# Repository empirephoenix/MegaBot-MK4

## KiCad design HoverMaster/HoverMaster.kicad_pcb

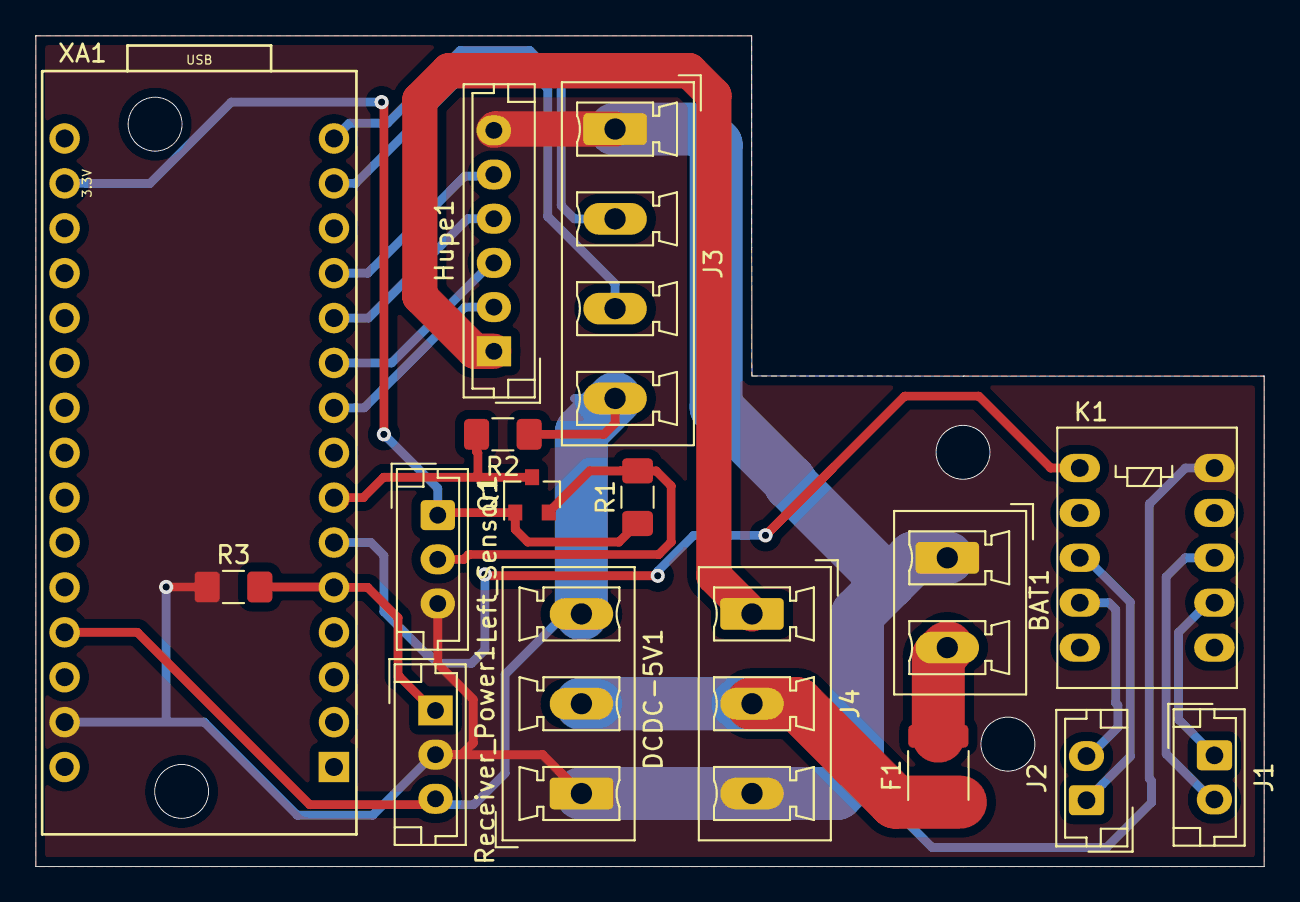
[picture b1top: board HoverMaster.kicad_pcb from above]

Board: 2 copper layers, 69.5 x 47.0 mm, 16 parts (0 on the bottom side), 20 nets.

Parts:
BAT1: Conn_01x02_Male; PhoenixContact_MCV_1,5_2-G-5.08_1x02_P5.08mm_Vertical
DCDC-5V1: Conn_01x03_Male; PhoenixContact_MCV_1,5_3-G-5.08_1x03_P5.08mm_Vertical
F1: Fuse; Fuse_1812_4532Metric_Pad1.30x3.40mm_HandSolder
Hupe1: Conn_01x06_Male; JST_EH_B06B-EH-A_1x06_P2.50mm_Vertical
J1, J2: Conn_01x02_Male; JST_EH_B2B-EH-A_1x02_P2.50mm_Vertical
J3: LED; PhoenixContact_MCV_1,5_4-G-5.08_1x04_P5.08mm_Vertical
J4: Conn_01x03_Female; PhoenixContact_MCV_1,5_3-G-5.08_1x03_P5.08mm_Vertical
K1: FRT5; Relay_DPDT_FRT5
Left_Sensor1: Conn_01x03; JST_EH_B3B-EH-A_1x03_P2.50mm_Vertical
Q1: BSS138; SOT-23
R1, R2: 10K; R_1206_3216Metric_Pad1.42x1.75mm_HandSolder
R3: 10kOhm; R_1206_3216Metric_Pad1.42x1.75mm_HandSolder
Receiver_Power1: Conn_01x04; JST_EH_B03B-EH-A_1x03_P2.50mm_Vertical
XA1: Arduino_Nano_Socket

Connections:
3.3V: Left_Sensor1.1, Q1.1, R1.1, XA1.3V3
5V: DCDC-5V1.3, J3.4, R2.1, Receiver_Power1.3, XA1.5V
12V: Hupe1.1, J4.1
BAT+: BAT1.2, F1.2
BAT_Fuse+: DCDC-5V1.2, F1.1, J4.2
GND: BAT1.1, DCDC-5V1.1, Hupe1.6, J3.1, J4.3, K1.10, Left_Sensor1.3, R3.1, Receiver_Power1.2, XA1.GND2
HOVER_POWER_RELAY: K1.1, XA1.D3
Hupe_1: Hupe1.2, XA1.D6
Hupe_2: Hupe1.3, XA1.D7
Hupe_3: Hupe1.4, XA1.D8
Hupe_4: Hupe1.5, XA1.D9
LED1: J3.2, XA1.D12
LED2: J3.3, XA1.D11
unnamed: J1.1, K1.7
unnamed: J1.2, K1.8
unnamed: J2.1, K1.3
unnamed: J2.2, K1.4
unnamed: Left_Sensor1.2, Q1.2, R1.2
PPM_IN: R3.2, Receiver_Power1.1, XA1.D2
PPM_OUT: Q1.3, R2.2, XA1.D4

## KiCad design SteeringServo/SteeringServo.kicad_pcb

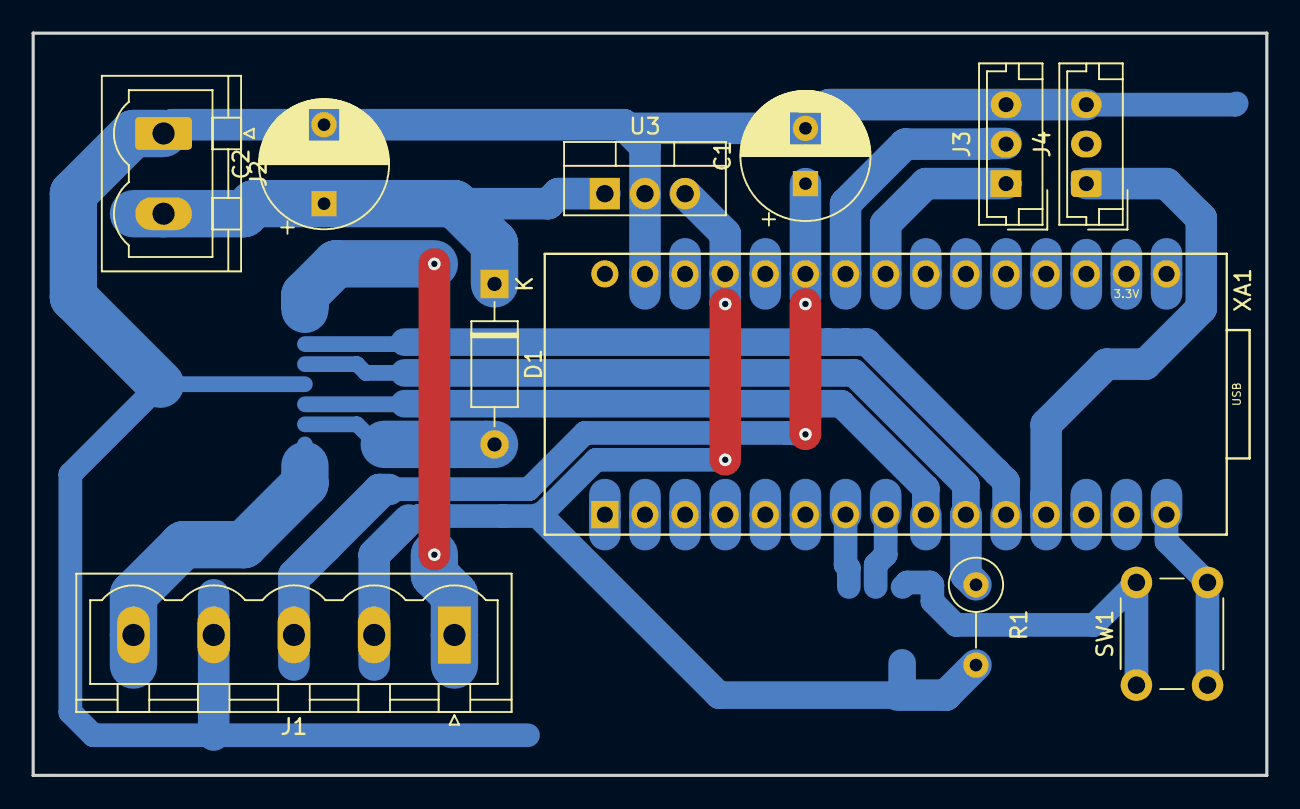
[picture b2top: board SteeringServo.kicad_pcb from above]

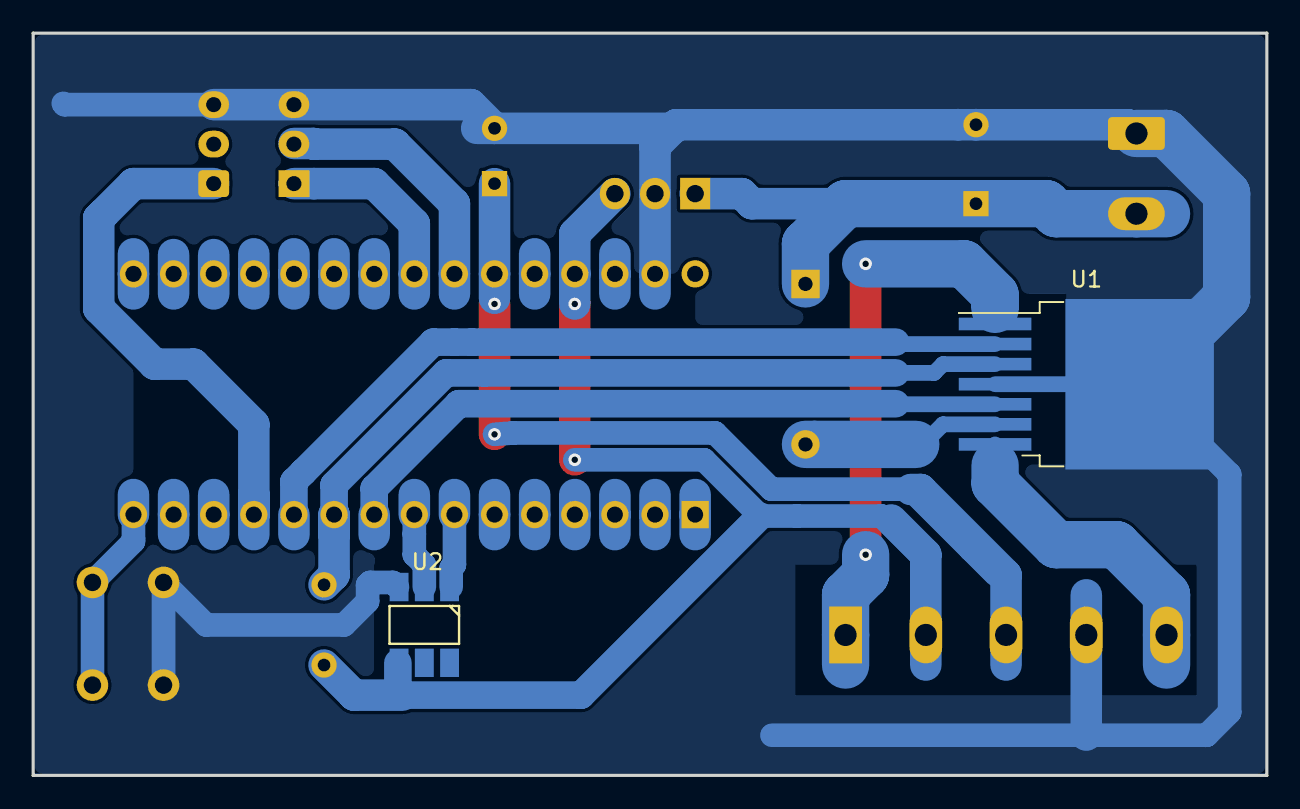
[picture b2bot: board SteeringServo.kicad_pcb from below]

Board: 2 copper layers, 78.1 x 47.0 mm, 13 parts (2 on the bottom side), 16 nets.

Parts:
C1: C; CP_Radial_D8.0mm_P3.50mm
C2: CP; CP_Radial_D8.0mm_P5.00mm
D1: DIODE; D_A-405_P10.16mm_Horizontal
J1: MotorConnector; PhoenixContact_MSTBVA_2,5_5-G-5,08_1x05_P5.08mm_Vertical
J2: To 12V Converter; PhoenixContact_MSTBVA_2,5_2-G-5,08_1x02_P5.08mm_Vertical
J3: Signal; JST_EH_B03B-EH-A_1x03_P2.50mm_Vertical
J4: Signal; JST_EH_B3B-EH-A_1x03_P2.50mm_Vertical
R1: R10k; R_Axial_DIN0309_L9.0mm_D3.2mm_P5.08mm_Vertical
SW1: SW_Push; SW_PUSH_6mm
U1: TLE5205; TO-263-7_TabPin4
U2: StatusLED; APA102_hand_solder
U3: L7805; TO-220-3_Vertical
XA1: Arduino_Nano_Socket

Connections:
5V: J1.2, R1.2, U2.4, U3.3, XA1.5V
12V: C2.1, D1.1, J2.2, U3.1
Calibrate: SW1.2, XA1.D12
GND: C1.2, C2.2, J1.4, J2.1, J3.3, J4.3, SW1.1, U1.4, U2.3, U3.2, XA1.GND2
LED_CIN: U2.2, XA1.D5
LED_DIN: U2.1, XA1.D4
M1: J1.1, U1.1
M2: J1.5, U1.7
M_ERR: U1.2, XA1.D8
M_IN_1: R1.1, U1.3, XA1.D7
M_IN_2: U1.5, XA1.D6
unnamed: D1.2, U1.6
SCL: J3.2, XA1.A5
SDA: J3.1, XA1.A4
SERVO_POTI: C1.1, J1.3, XA1.A6
Signal: J4.1, XA1.D9

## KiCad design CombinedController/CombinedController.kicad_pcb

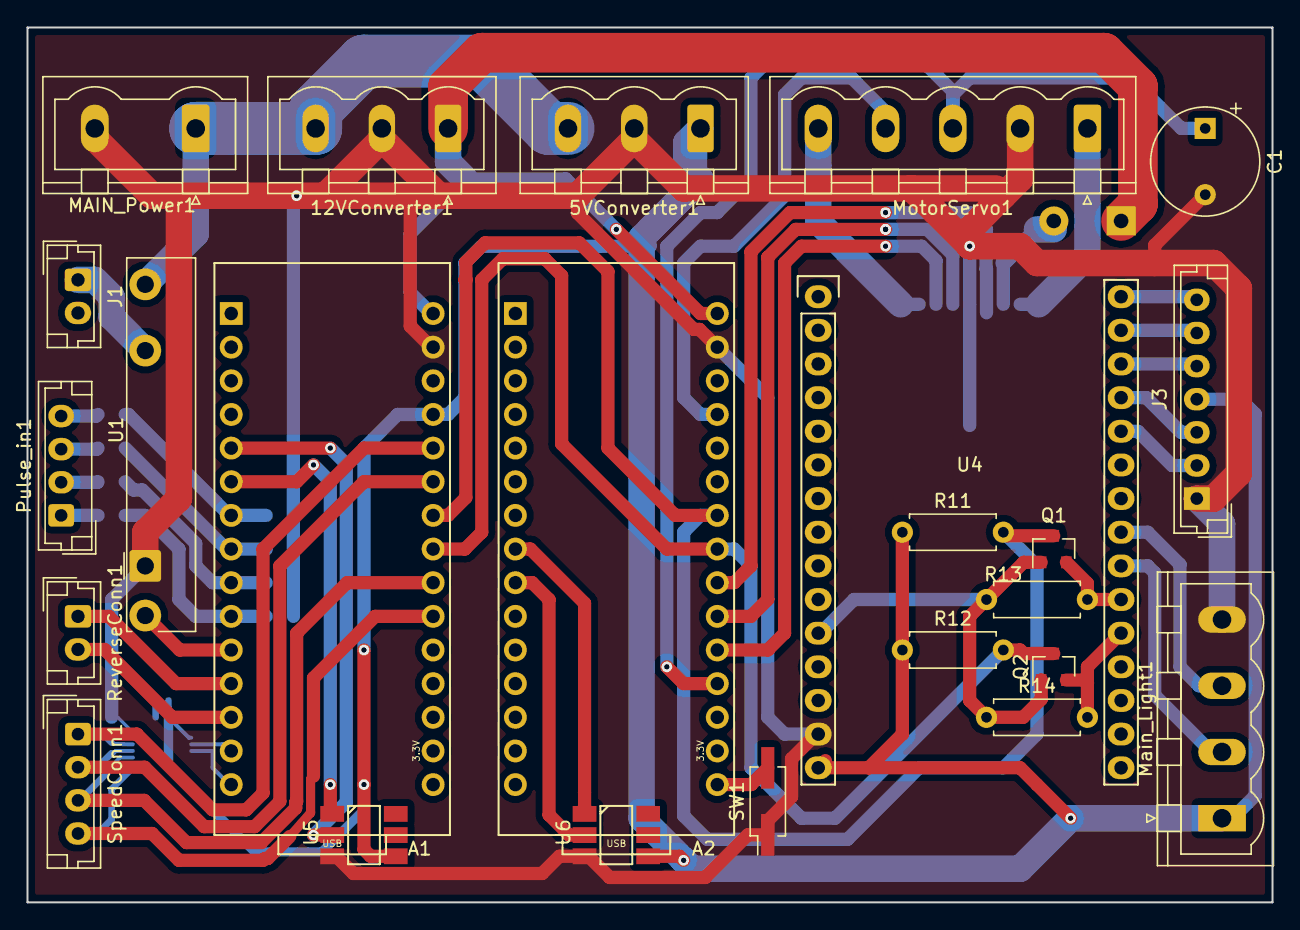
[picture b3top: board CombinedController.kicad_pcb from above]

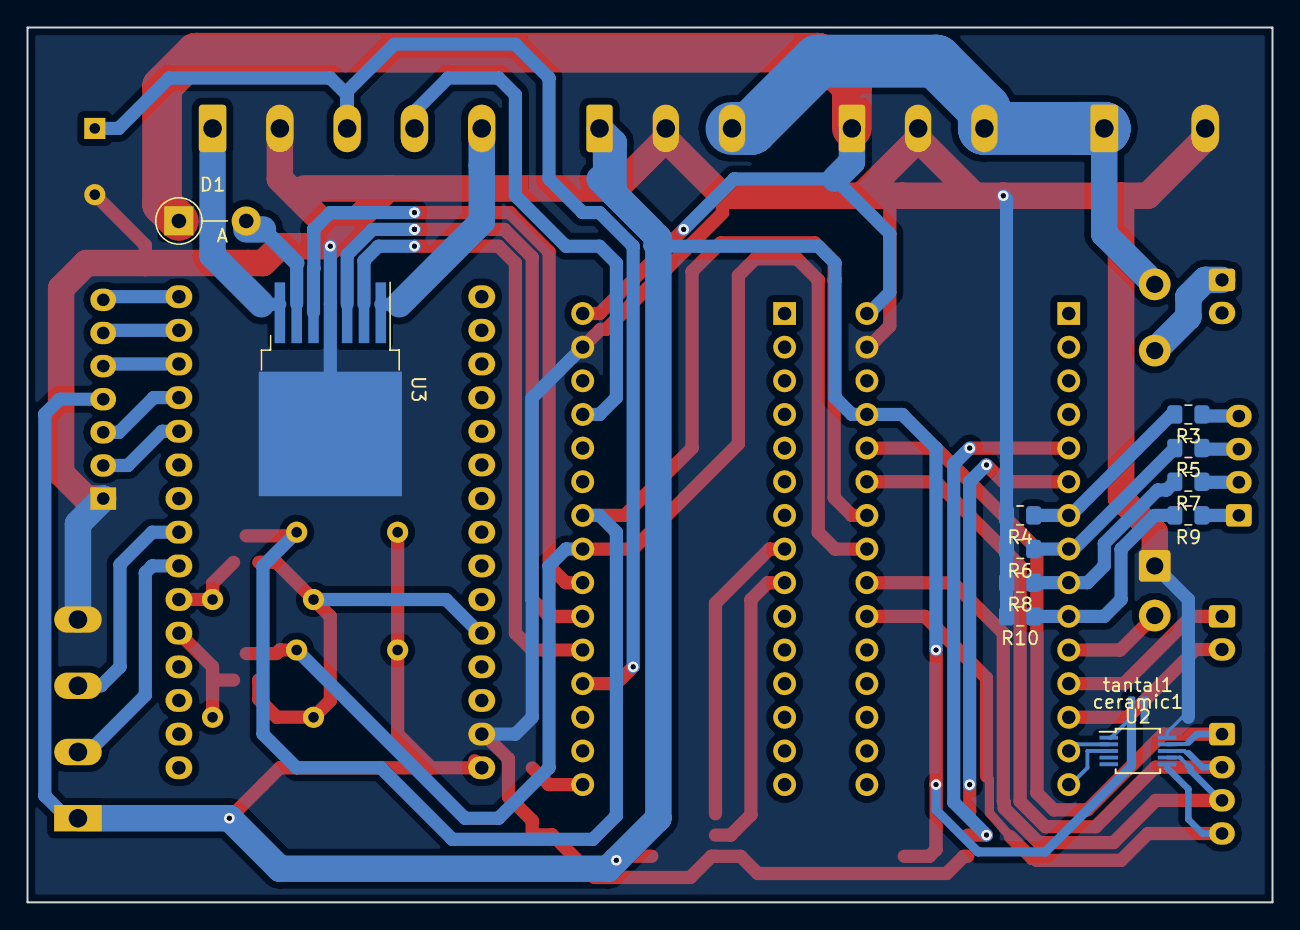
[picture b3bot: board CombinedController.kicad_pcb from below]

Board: 2 copper layers, 94.0 x 66.0 mm, 37 parts (13 on the bottom side), 47 nets.

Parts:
5VConverter1: Conn_01x04_Male; PhoenixContact_MSTBVA_2,5_3-G_1x03_P5.00mm_Vertical
12VConverter1: Conn_01x03_Male; PhoenixContact_MSTBVA_2,5_3-G_1x03_P5.00mm_Vertical
A1, A2: Arduino_Nano_v3.x; Arduino_Nano_Socket
C1: C; CP_Radial_Tantal_D8.0mm_P5.00mm
D1: DIODE; D_DO-41_SOD81_P5.08mm_Vertical_AnodeUp
J1: PWR_C; JST_EH_B02B-EH-A_1x02_P2.50mm_Vertical
J3: Conn_01x11_Male; JST_EH_B07B-EH-A_1x07_P2.50mm_Vertical
MAIN_Power1: Conn_01x02_Male; PhoenixContact_GMSTBVA_2,5_2-G-7,62_1x02_P7.62mm_Vertical
Main_Light1: Conn_01x02_Male; PhoenixContact_MSTBVA_2,5_4-G_1x04_P5.00mm_Vertical
MotorServo1: Conn_01x05_Female; PhoenixContact_MSTBVA_2,5_5-G-5,08_1x05_P5.08mm_Vertical
Pulse_in1: Conn_01x04_Male; JST_EH_B04B-EH-A_1x04_P2.50mm_Vertical
Q1, Q2: BSS138; SOT-23
R3, R4, R5, R6, R7, R8: R; R_0805_2012Metric_Pad1.15x1.40mm_HandSolder
R9: 10kohm; R_0805_2012Metric_Pad1.15x1.40mm_HandSolder
R10: 1kohm; R_0805_2012Metric_Pad1.15x1.40mm_HandSolder
R11, R12, R13, R14: R; R_Axial_DIN0207_L6.3mm_D2.5mm_P7.62mm_Horizontal
ReverseConn1: Conn_01x02_Male; JST_EH_B02B-EH-A_1x02_P2.50mm_Vertical
SW1: SW_Push; PinHeader_2x01_P2.54mm_Vertical_SMD
SpeedConn1: Conn_01x04_Male; JST_EH_B04B-EH-A_1x04_P2.50mm_Vertical
U1: 34.81-8240; Finder_34.81
U2: MCP4728; MSOP-10_3x3mm_P0.5mm
U3: TLE5205; TO-263-7_TabPin4
U4: NodeMCU_Amica_R2
U5, U6: SK9822; APA102_hand_solder
ceramic1: 0.1uF; C_0402_1005Metric
tantal1: 10uF; C_0402_1005Metric

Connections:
3.3V_1: Q1.1, Q2.1, R13.1, R14.1, U4.11
5V_2: A2.5V, MotorServo1.4
5V_Main: 5VConverter1.1, A1.5V, J3.4, Main_Light1.1, R11.1, R12.1, U2.1, U4.15, U5.4, U6.4, ceramic1.1, tantal1.1
12V: 12VConverter1.1, A1.VIN, A2.VIN, D1.1
EF: A2.A1, U3.2
GND: 5VConverter1.2, 12VConverter1.2, A1.GND2, A2.GND2, C1.2, J3.1, MAIN_Power1.2, Main_Light1.4, MotorServo1.2, R4.2, R6.2, R8.2, R10.2, SW1.1, U1.A1, U2.10, U3.4, U4.14, U5.3, U6.3, ceramic1.2, tantal1.2
IN1: A2.A2, U3.3
IN2: A2.A3, U3.5
unnamed: 5VConverter1.3, 12VConverter1.3, MAIN_Power1.1, U1.14
unnamed: A1.D2, U5.2
unnamed: A1.D3, U5.1
unnamed: A1.D9, ReverseConn1.1
unnamed: A1.D10, ReverseConn1.2
unnamed: A2.D5, U6.1
unnamed: A2.D6, U6.2
unnamed: A2.D13, SW1.2
unnamed: D1.2, U3.6
unnamed: J1.1, U1.11
unnamed: J3.2, U4.26
unnamed: J3.3, U4.27
unnamed: J3.5, U4.28
unnamed: J3.6, U4.29
unnamed: J3.7, U4.30
unnamed: Main_Light1.2, U4.22
unnamed: Main_Light1.3, U4.23
unnamed: MotorServo1.1, U3.7
unnamed: MotorServo1.5, U3.1
unnamed: Pulse_in1.1, R9.1
unnamed: Pulse_in1.2, R7.1
unnamed: Pulse_in1.3, R5.1
unnamed: Pulse_in1.4, R3.1
P_IN_A: A1.D4, R3.2, R4.1
P_IN_B: A1.D5, R5.2, R6.1
P_IN_C: A1.D6, R7.2, R8.1
P_IN_D: A1.D7, R9.2, R10.1
Power_Relay: A1.D8, U1.A2
SCL_DA: A1.D11, U2.2
SCL_H: A1.A5, A2.A5, Q1.3, R11.2
SCL_L: Q1.2, R13.2, U4.21
SDA_DA: A1.D12, U2.3
SDA_H: A1.A4, A2.A4, Q2.3, R12.2
SDA_L: Q2.2, R14.2, U4.20
SERVO_In: A2.A0, C1.1, MotorServo1.3
VOUTA: A1.A2, SpeedConn1.4, U2.6
VOUTB: A1.A3, SpeedConn1.3, U2.7
VOUTC: A1.A6, SpeedConn1.2, U2.8
VOUTD: A1.A7, SpeedConn1.1, U2.9

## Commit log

2018-12-07 initial start of mk4
2018-12-14 combined controller
2018-12-14 Add MC33886 Footprint and fix schematics
2019-01-16 TLE5205 added
2019-01-16 added tle started pcb layouting
2019-01-20 pcb initial
2019-01-20 initial cnc working
2019-04-01 pcb for servo
2019-04-01 readded legacy servo support
2019-04-01 added old sourcecode to be reused
2019-04-02 adjusted sterring code
2019-04-02 improved layout
2019-04-03 reduced brightness, fixed calbiration pin inputmode
2019-04-04 pwm support and fastgpio use
2019-04-07 made servo code more useable
2019-04-10 prevent nano from buring the am1117 when being powered by usb
2019-04-11 initial version of hovermaster
2019-04-16 fixed multiple issues with servocontroller
2019-05-10 hovermaster
2019-05-29 new routing
2019-06-19 initial led support, warning lights in emergency mode
2019-06-26 ppm communication & dynamic light modes
2019-07-05 fix for power management
2019-07-10 steering support
2019-08-02 new controller design
2019-10-11 new master
2019-10-18 arduino
2019-10-18 added gnd plates
2019-10-19 switch to code due to isp programmer issues
2019-10-19 initial startup fix, ppm is intially valid for a few ms
2019-10-20 fixed missing ppm in filter resistor
